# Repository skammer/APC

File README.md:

# Atari Punk Console

> With voltage control inputs

Once upon a time I was bored and decided to try something new. Ordering a bunch
of PCBs from China seemed novel enough, and so my quest began.

I chose to go with [APC](https://en.wikipedia.org/wiki/Atari_Punk_Console) as
it is super simple to build and does very characteristic noises, so it would be
very easy to identify problems with the circuit even without an oscilloscope.

You will need [KiCAD](http://kicad-pcb.org/) if you with to view the schematics,
but you can just straight up download `gerbers.zip` and use that to have your
own batch of PCBs made. That's exactly the same zip file I used to make mine,
so I'm reasonably confident it should not be broken.

For manufacturing I chose to go with PCBway, mostly because every DIY youtuber
ran at least one ad for them at some point.

Here is my referral link, if you haven't signed up for PCBway yet:
https://www.pcbway.com/setinvite.aspx?inviteid=254952

I can't really provide any concrete part numbers for connectors, as I just got
whatever was available at the local electronics store, but here's a list anyway:

```
Qty Item
1   LM556 IC
2   500k potentiometer
3   Mono audio jack
1   Center ground DC barrel jack (the ones used on guitar pedals)
1   LED
2   1k resistor
1   4.7k resistor
1   10k resistor
1   0.01uF capacitor
2   0.1uF capacitor
2   10uF electrolytic capacitor
1   SPST switch
```

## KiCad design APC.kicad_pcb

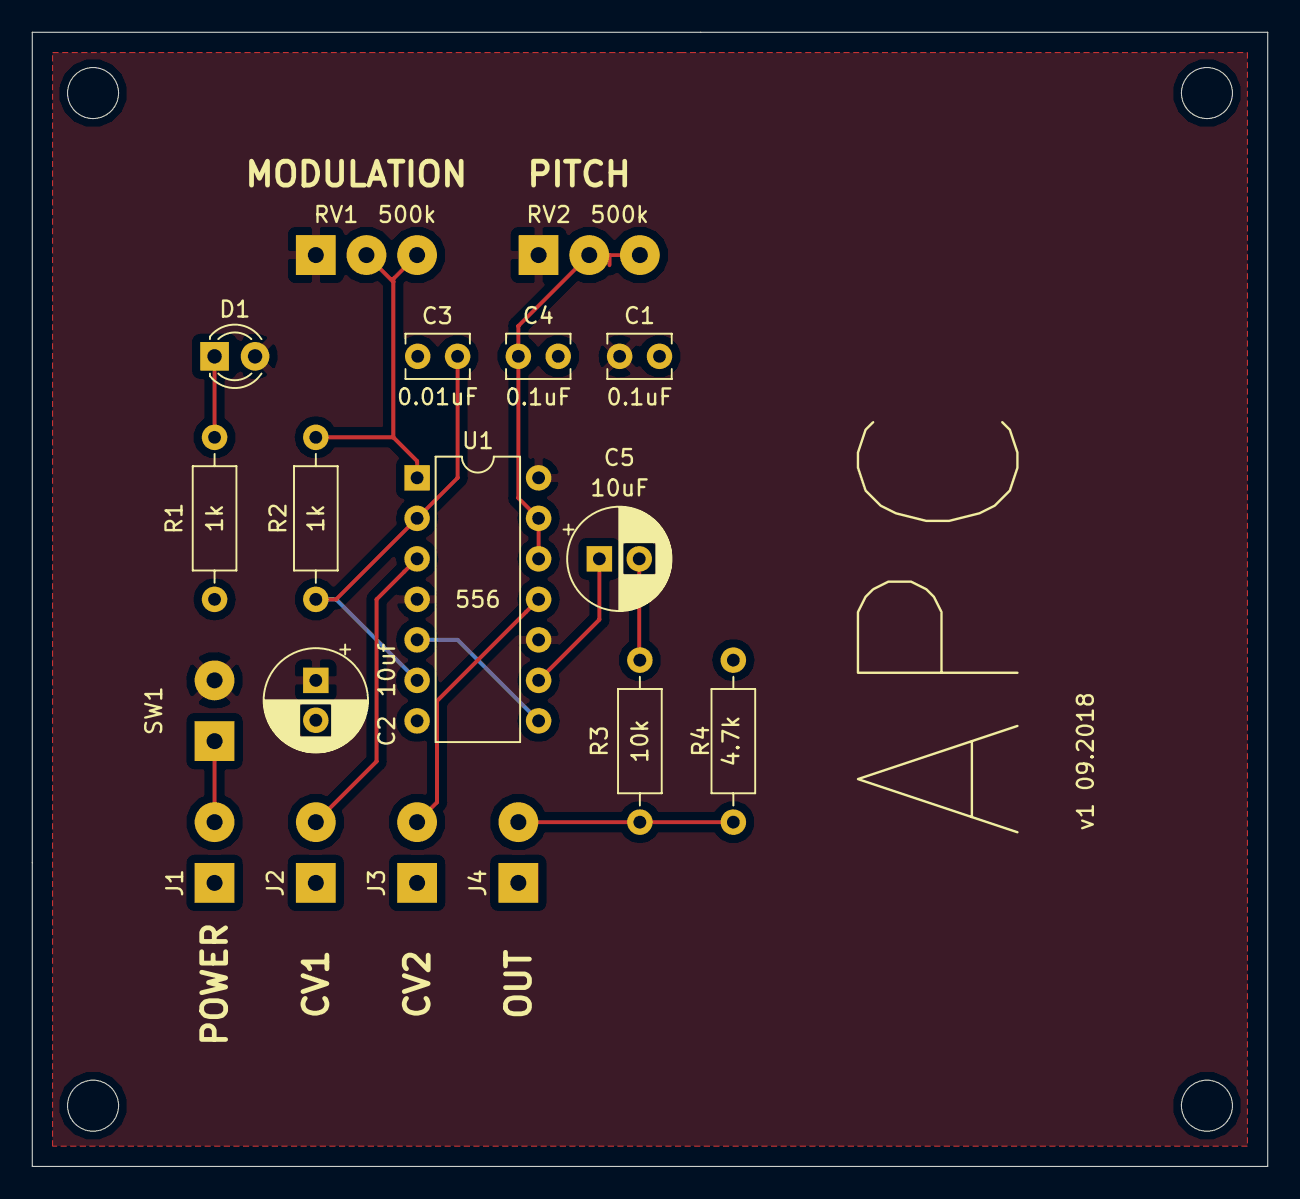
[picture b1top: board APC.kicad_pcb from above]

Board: 2 copper layers, 77.5 x 71.1 mm, 22 parts (0 on the bottom side), 13 nets.

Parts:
 : MountingHole_3.2mm_M3
 #2,  #3,  #4: MountingHole_3.2mm_M3
C1, C4: 0.1uF; C_Disc_D3.8mm_W2.6mm_P2.50mm
C2: 10uf; CP_Radial_D6.3mm_P2.50mm
C3: 0.01uF; C_Disc_D3.8mm_W2.6mm_P2.50mm
C5: 10uF; CP_Radial_D6.3mm_P2.50mm
D1: LED; LED_D3.0mm
J1: DC Center Ground; SolderWirePad_1x02_P3.81mm_Drill1mm
J2: MONO JACK CV1; SolderWirePad_1x02_P3.81mm_Drill1mm
J3: MONO JACK CV2; SolderWirePad_1x02_P3.81mm_Drill1mm
J4: MONO_JACK OUT; SolderWirePad_1x02_P3.81mm_Drill1mm
R1, R2: 1k; R_Axial_DIN0207_L6.3mm_D2.5mm_P10.16mm_Horizontal
R3: 10k; R_Axial_DIN0207_L6.3mm_D2.5mm_P10.16mm_Horizontal
R4: 4.7k; R_Axial_DIN0207_L6.3mm_D2.5mm_P10.16mm_Horizontal
RV1, RV2: 500k; SolderWirePad_1x03_P3.175mm_Drill1mm
SW1: SW_SPST; SolderWirePad_1x02_P3.81mm_Drill1mm
U1: LM556; DIP-14_W7.62mm

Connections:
+9V: J1.2, SW1.1
/PWR: C1.1, C2.1, D1.2, RV1.1, RV2.1, SW1.2, U1.4, U1.10, U1.14
GND: C1.2, C2.2, C3.2, C4.2, J1.1, J2.1, J3.1, J4.1, R1.2, R4.2, U1.7
unnamed: C3.1, R2.1, U1.2, U1.6
unnamed: C4.1, RV2.2, RV2.3, U1.12, U1.13
unnamed: C5.1, U1.9
unnamed: C5.2, R3.1
unnamed: D1.1, R1.1
unnamed: J2.2, U1.3
unnamed: J3.2, U1.11
unnamed: J4.2, R3.2, R4.1
unnamed: R2.2, RV1.2, RV1.3, U1.1
unnamed: U1.5, U1.8
